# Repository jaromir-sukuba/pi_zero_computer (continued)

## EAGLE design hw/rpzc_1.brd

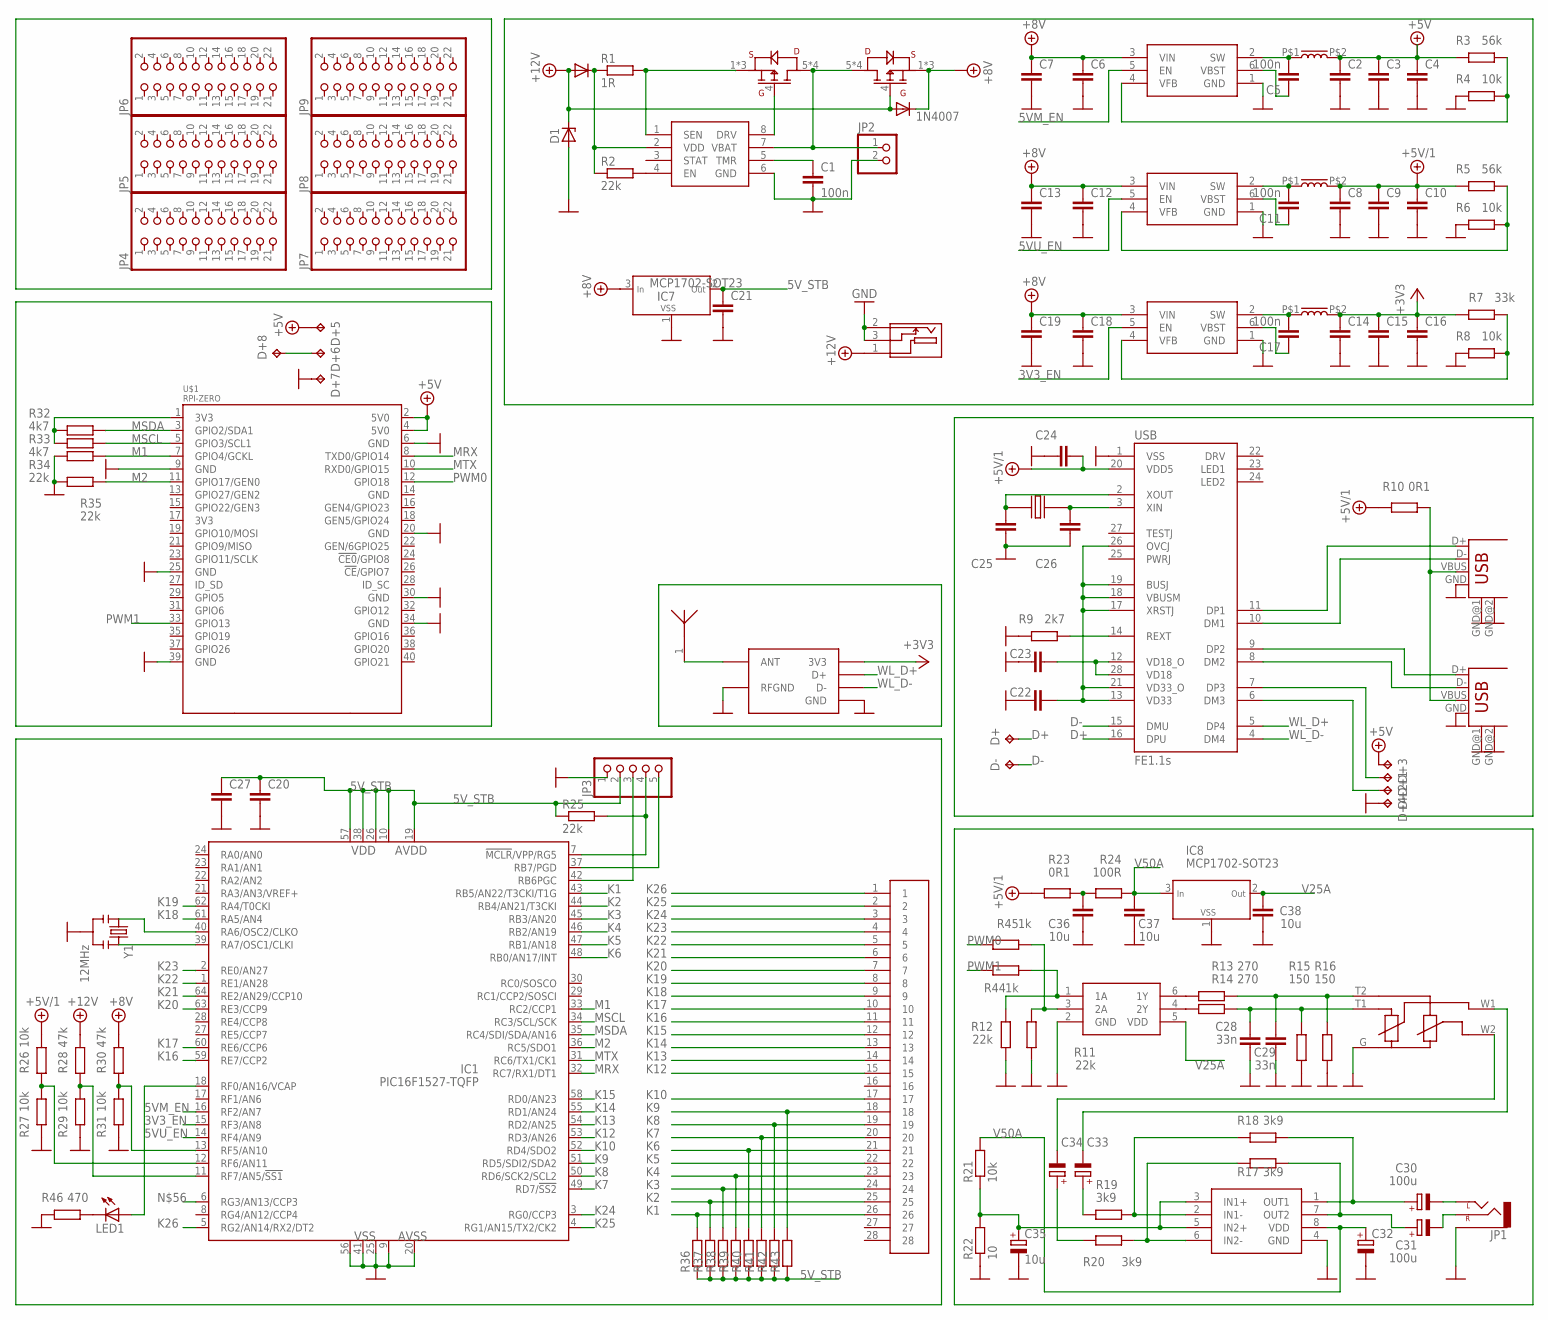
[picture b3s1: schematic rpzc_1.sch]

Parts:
ANT1: ANT_RAINSUN_24GHZ; ANT_RAINSUN-24G
C1, C5, C11, C17: 100n; R0805
C2, C3, C4, C6, C7, C8, C9, C10, C12, C13, C14, C15, C16, C18, C19, C20, C21, C22, C23, C24, C25, C26, C27: C_0806; R0805
C28, C29: 33n; R0805
C30, C31: 100u; PANASONIC_D
C32: CPOL-EUD; PANASONIC_D
C33, C34: CPOL-EUB; PANASONIC_B
C35: 10u; PANASONIC_B
C36, C37, C38: 10u; R0805
CON1: CONN-28_1_K; CONN_FFC_28_1_K
D1: ZENER-DIODESMB; SMB
D2: 1N4007; SMB
D5: DIODE-SMB; SMB
D+, D+1, D+2, D+3, D+4, D+5, D+6, D+7, D+8: TPTP14R; TP14R
D-: TPTP14R; TP14R
IC1: PIC16F1527-TQFP; TQFP64-10X10
IC2: 74LVC2G34; SOT23-6
IC3, IC5, IC6: TPS562200; SOT23-6
IC4: MCP73844; MSOP8
IC7, IC8: MCP1702-SOT23; SOT23
JP1: AUDIO-JACKPTH; AUDIO-JACK
JP2: PINHD-1X02_2.54-90°; 1X02/90
JP3: PINHD-1X05_2.00; 1X05M
JP4, JP5, JP6, JP7, JP8, JP9: PINHD-2X11_2.54; 2X11
LED1: LEDCHIPLED_0805; CHIPLED_0805
MOD1: MOD_USB_RTL8188
R1: 1R; R1206
R2, R11, R12, R25, R34, R35: 22k; R0805
R3, R5: 56k; R0805
R4, R6, R8, R21, R26, R27, R29, R31: 10k; R0805
R7: 33k; R0805
R9: 2k7; R0805
R10, R23: 0R1; R1206
R13, R14: 270; R0805
R15, R16: 150; R0805
R17, R18, R19, R20: 3k9; R0805
R22: 10; R0805
R24: 100R; R0805
R28, R30: 47k; R0805
R32, R33: 4k7; R0805
R36, R37, R38, R39, R40, R41, R42, R43: R_0805; R0805
R44, R45: 1k; R0805
R46: 470; R0805
T1, T2: PFET_SO8; SO-08
U$1: RPI-ZERO; RASPBERRYPI_BASTELSTUBE_V13_RASPI_BOARD_B+_FULL
U$2: POT_DUAL_14X2; POT_14X2DUAL
U$3: TDA1308; SO-08
U$4, U$5, U$8: 2u2; BOURNS_SRP7030
U$6: CONN_DC_13; CON_DC13
USB: FE1.1S; FE1.1S_SSOP-28
USB1, USB2: USB-A-H
X1: CRYST_TC26TC38; TC38
Y1: 12MHz; RESONATOR-SMD

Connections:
3V3@1: R32.1, R33.1, U$1.1 (3V3)
3V3_EN: IC1.15 (RF3/AN8), IC6.5 (EN)
5VM_EN: IC1.16 (RF2/AN7), IC3.5 (EN)
5VU_EN: IC1.14 (RF4/AN9), IC5.5 (EN)
5V_STB: C20.1, C21.1, C27.1, IC1.10 (VDD), IC1.19 (AVDD), IC1.26 (VDD), IC1.38 (VDD), IC1.57 (VDD), IC7.2 (OUT), JP3.2, R25.1, R36.1, R37.1, R38.1, R39.1, R40.1, R41.1, R42.1, R43.1
+3V3: C14.1, C15.1, C16.1, MOD1.3V3, R7.1, U$5.P$2
+5V: C2.1, C3.1, C4.1, D+3.TP, D+5.TP, R3.1, U$1.2 (5V0), U$1.4 (5V0), U$8.P$2
+5V/1: C8.1, C9.1, C10.1, C24.2, R5.1, R10.2, R23.2, R26.2, U$4.P$2, USB.20 (VDD5)
+8V: C6.1, C7.1, C12.1, C13.1, C18.1, C19.1, D2.C, IC3.3 (VIN), IC5.3 (VIN), IC6.3 (VIN), IC7.3 (IN), R30.2, T2.1 (S), T2.2 (S), T2.3 (S)
+12V: D1.C, D2.A, D5.A, R28.2, T2.4 (G), U$6.1
D+: D+.TP, USB.16 (DPU)
D-: D-.TP, USB.15 (DMU)
GND: C1.2, C2.2, C3.2, C4.2, C6.2, C7.2, C8.2, C9.2, C10.2, C12.2, C13.2, C14.2, C15.2, C16.2, C18.2, C19.2, C20.2, C21.2, C22.1, C23.1, C24.1, C25.1, C26.1, C27.2, C28.1, C29.1, C32.-, C35.-, C36.1, C37.1, C38.1, D1.A, D+4.TP, D+7.TP, IC1.9 (VSS), IC1.20 (AVSS), IC1.25 (VSS), IC1.41 (VSS), IC1.56 (VSS), IC2.2 (GND), IC3.1 (GND), IC4.6 (GND), IC5.1 (GND), IC6.1 (GND), IC7.1 (VSS), IC8.1 (VSS), JP1.SLEEVE, JP2.2, JP3.1, MOD1.GND, MOD1.RFGND, R4.1, R6.1, R8.1, R9.1, R11.1, R12.1, R15.2, R16.2, R22.1, R27.1, R29.1, R31.1, R34.1, R35.1, R46.1, U$1.6 (GND), U$1.9 (GND), U$1.20 (GND), U$1.25 (GND), U$1.30 (GND), U$1.34 (GND), U$1.39 (GND), U$2.G, U$3.4 (GND), U$6.2 (N), U$6.3 (SW), USB.1 (VSS), USB1.GND, USB1.GND@1 (GND), USB1.GND@2 (GND), USB2.GND, USB2.GND@1 (GND), USB2.GND@2 (GND), Y1.2
K1: CON1.26, IC1.43 (RB5/AN22/T3CKI/T1G), R36.2
K2: CON1.25, IC1.44 (RB4/AN21/T3CKI), R37.2
K3: CON1.24, IC1.45 (RB3/AN20), R38.2
K4: CON1.23, IC1.46 (RB2/AN19), R39.2
K5: CON1.22, IC1.47 (RB1/AN18)
K6: CON1.21, IC1.48 (RB0/AN17/INT), R40.2
K7: CON1.20, IC1.49 (RD7/!SS2), R41.2
K8: CON1.19, IC1.50 (RD6/SCK2/SCL2), R42.2
K9: CON1.18, IC1.51 (RD5/SDI2/SDA2), R43.2
K10: CON1.17, IC1.52 (RD4/SDO2)
K12: CON1.15, IC1.53 (RD3/AN26)
K13: CON1.14, IC1.54 (RD2/AN25)
K14: CON1.13, IC1.55 (RD1/AN24)
K15: CON1.12, IC1.58 (RD0/AN23)
K16: CON1.11, IC1.59 (RE7/CCP2)
K17: CON1.10, IC1.60 (RE6/CCP6)
K18: CON1.9, IC1.61 (RA5/AN4)
K19: CON1.8, IC1.62 (RA4/T0CKI)
K20: CON1.7, IC1.63 (RE3/CCP9)
K21: CON1.6, IC1.64 (RE2/AN29/CCP10)
K22: CON1.5, IC1.1 (RE1/AN28)
K23: CON1.4, IC1.2 (RE0/AN27)
K24: CON1.3, IC1.3 (RG0/CCP3)
K25: CON1.2, IC1.4 (RG1/AN15/TX2/CK2)
K26: CON1.1, IC1.5 (RG2/AN14/RX2/DT2)
M1: IC1.33 (RC2/CCP1), R34.2, U$1.7 (GPIO4/GCKL)
M2: IC1.36 (RC5/SDO1), R35.2, U$1.11 (GPIO17/GEN0)
MRX: IC1.32 (RC7/RX1/DT1), U$1.8 (TXD0/GPIO14)
MSCL: IC1.34 (RC3/SCL/SCK), R33.2, U$1.5 (GPIO3/SCL1)
MSDA: IC1.35 (RC4/SDI/SDA/AN16), R32.2, U$1.3 (GPIO2/SDA1)
MTX: IC1.31 (RC6/TX1/CK1), U$1.10 (RXD0/GPIO15)
unnamed: C5.2, IC3.2 (SW), U$8.P$1
unnamed: D5.C, IC4.2 (VDD), R1.1, R2.1
unnamed: IC4.1 (SEN), R1.2, T1.1 (S), T1.2 (S), T1.3 (S)
unnamed: IC4.8 (DRV), T1.4 (G)
unnamed: IC4.4 (EN), R2.2
unnamed: C1.1, IC4.5 (TMR)
unnamed: IC4.7 (VBAT), JP2.1, T1.5 (D), T1.6 (D), T1.7 (D), T1.8 (D), T2.5 (D), T2.6 (D), T2.7 (D), T2.8 (D)
unnamed: USB.9 (DP2), USB2.D+
unnamed: USB.8 (DM2), USB2.D-
unnamed: USB.10 (DM1), USB1.D-
unnamed: USB.11 (DP1), USB1.D+
unnamed: C22.2, USB.13 (VD33), USB.17 (XRSTJ), USB.18 (VBUSM), USB.19 (BUSJ), USB.21 (VD33_O), USB.26 (OVCJ)
unnamed: C5.1, IC3.6 (VBST)
unnamed: IC3.4 (VFB), R3.2, R4.2
unnamed: C23.2, USB.12 (VD18_O), USB.28 (VD18)
unnamed: R9.2, USB.14 (REXT)
unnamed: C11.2, IC5.2 (SW), U$4.P$1
unnamed: C25.2, USB.2 (XOUT), X1.P$1
unnamed: C11.1, IC5.6 (VBST)
unnamed: IC5.4 (VFB), R5.2, R6.2
unnamed: C26.2, USB.3 (XIN), X1.P$2
unnamed: C17.2, IC6.2 (SW), U$5.P$1
unnamed: R10.1, USB1.VBUS, USB2.VBUS
unnamed: C17.1, IC6.6 (VBST)
unnamed: IC6.4 (VFB), R7.2, R8.2
unnamed: IC2.6 (1Y), R13.2
unnamed: IC2.4 (2Y), R14.2
unnamed: C29.2, R13.1, R16.1, U$2.T2
unnamed: C28.2, R14.1, R15.1, U$2.T1
unnamed: ANT1.1, MOD1.ANT
unnamed: C30.-, JP1.TIP (LEFT)
unnamed: C31.-, JP1.RING (RIGHT)
unnamed: C30.+, R18.2, U$3.1 (OUT1)
unnamed: C31.+, R17.2, U$3.7 (OUT2)
unnamed: C35.+, R21.1, R22.2, U$3.3 (IN1+), U$3.5 (IN2+)
unnamed: R18.1, R19.2, U$3.2 (IN1-)
unnamed: R17.1, R20.2, U$3.6 (IN2-)
unnamed: C33.+, R19.1
unnamed: C34.+, R20.1
unnamed: C34.-, U$2.W2
unnamed: C33.-, U$2.W1
unnamed: D+1.TP, USB.7 (DP3)
unnamed: D+2.TP, USB.6 (DM3)
unnamed: C36.2, R23.1, R24.1
unnamed: IC1.12 (RF6/AN11), R26.1, R27.2
unnamed: IC1.7 (!MCLR!/VPP/RG5), JP3.4, R25.2
unnamed: IC1.37 (RB7/PGD), JP3.5
unnamed: IC1.42 (RB6PGC), JP3.3
unnamed: IC1.11 (RF7/AN5/!SS1), R28.1, R29.2
unnamed: IC1.40 (RA6/OSC2/CLKO), Y1.1
unnamed: IC1.39 (RA7/OSC1/CLKI), Y1.3
unnamed: IC1.13 (RF5/AN10), R30.1, R31.2
unnamed: D+6.TP, D+8.TP
unnamed: IC2.3 (2A), R11.2, R45.1
unnamed: IC2.1 (1A), R12.2, R44.1
unnamed: LED1.C, R46.2
unnamed: IC1.18 (RF0/AN16/VCAP), LED1.A
PWM0: R45.2, U$1.12 (GPIO18)
PWM1: R44.2, U$1.33 (GPIO13)
V25A: C38.2, IC2.5 (VDD), IC8.2 (OUT)
V50A: C32.+, C37.2, IC8.3 (IN), R21.2, R24.2, U$3.8 (VDD)
WL_D+: MOD1.D+, USB.5 (DP4)
WL_D-: MOD1.D-, USB.4 (DM4)

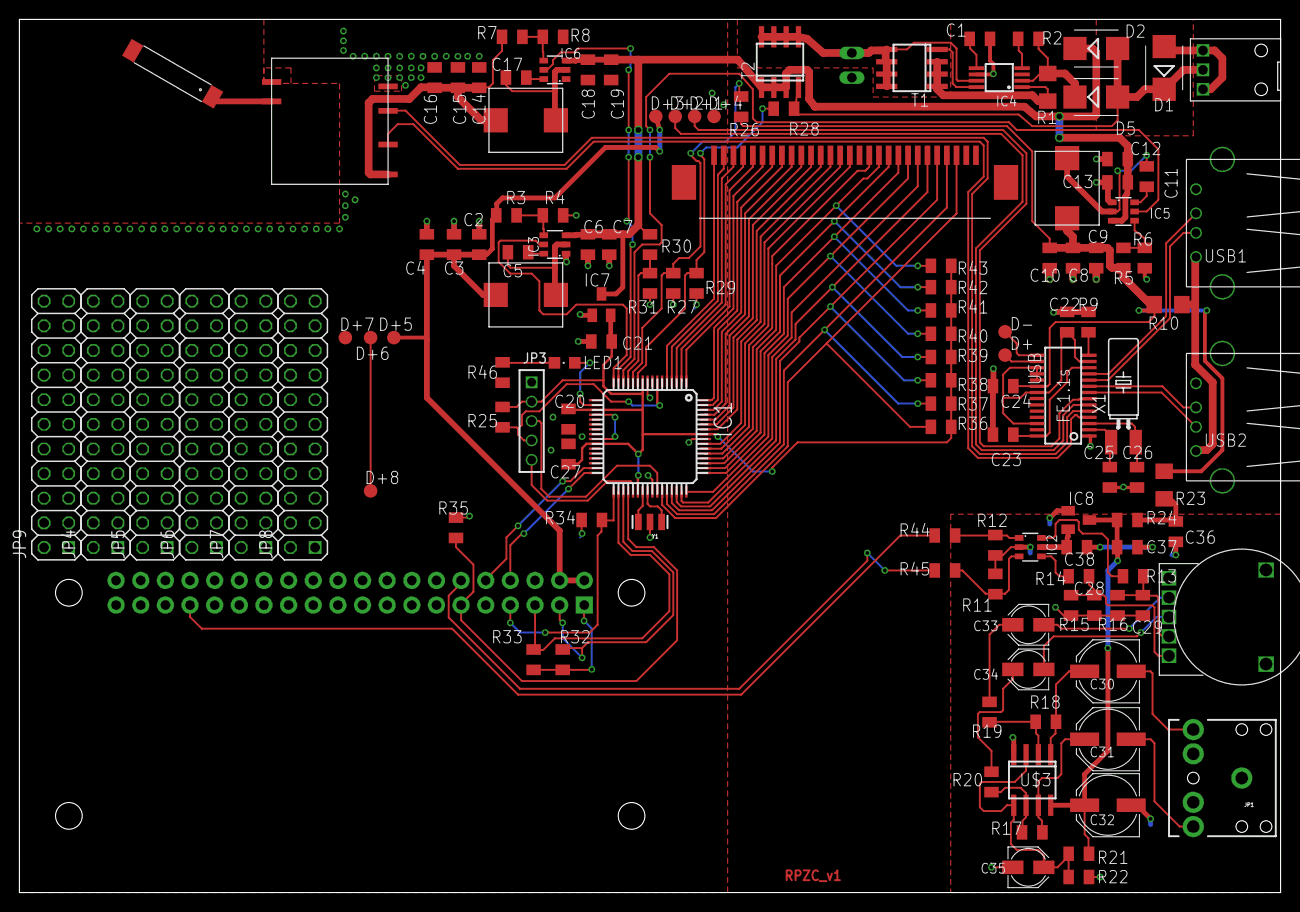
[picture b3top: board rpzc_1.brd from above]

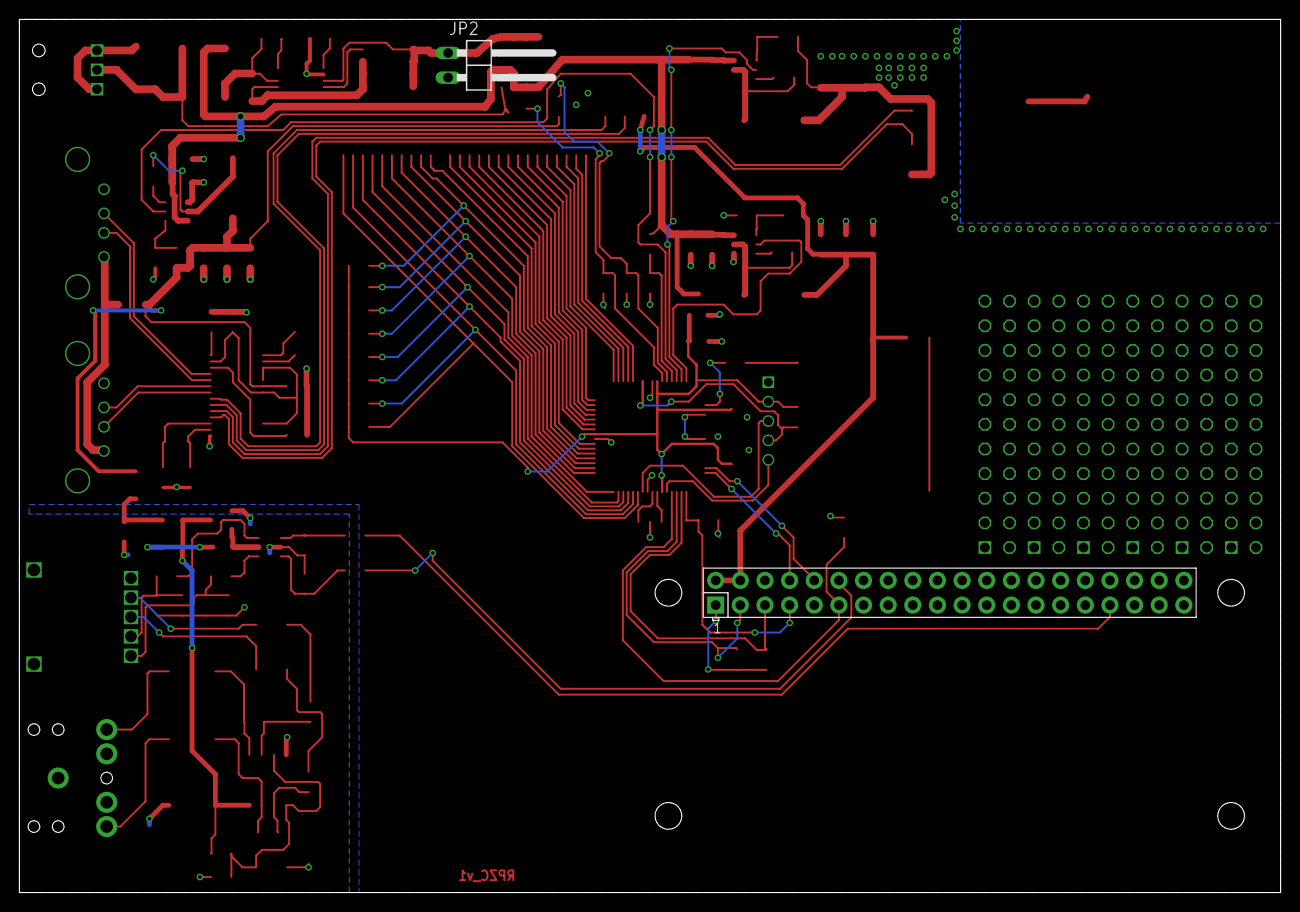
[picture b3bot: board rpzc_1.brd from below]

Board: 2 copper layers, 130.0 x 90.0 mm, 132 parts (2 on the bottom side), 107 nets.

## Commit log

2017-01-14 :circus_tent: Added .gitattributes & .gitignore files
2017-01-14 first hw
2017-03-31 new version, a bit messy
2017-03-31 readme update
2017-07-24 rev 2
2017-07-25 rev 3
    added mechanical files, BOM
